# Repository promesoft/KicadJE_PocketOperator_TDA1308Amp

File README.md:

# KicadJE_PocketOperator_TDA1308Amp
TDA1308 based headphone power amp for Teenage Engineering PO series

# Version - REV A1
Tested Working - multi channel input
Not tested - sync

# Kicad 9

# Purpose AMP
- Amp and sync dist for PO TE boards
- Overcome the drop in audio level that happens when daisychaining the devices
- 
# Operation
## Amp 1
- 2 stereo in
- 1 mono / sync in
- 2 sync out
- 1 stereo headphone out
- power button

# Pictures

Components:
https://www.aliexpress.com/item/1005007083484555.html

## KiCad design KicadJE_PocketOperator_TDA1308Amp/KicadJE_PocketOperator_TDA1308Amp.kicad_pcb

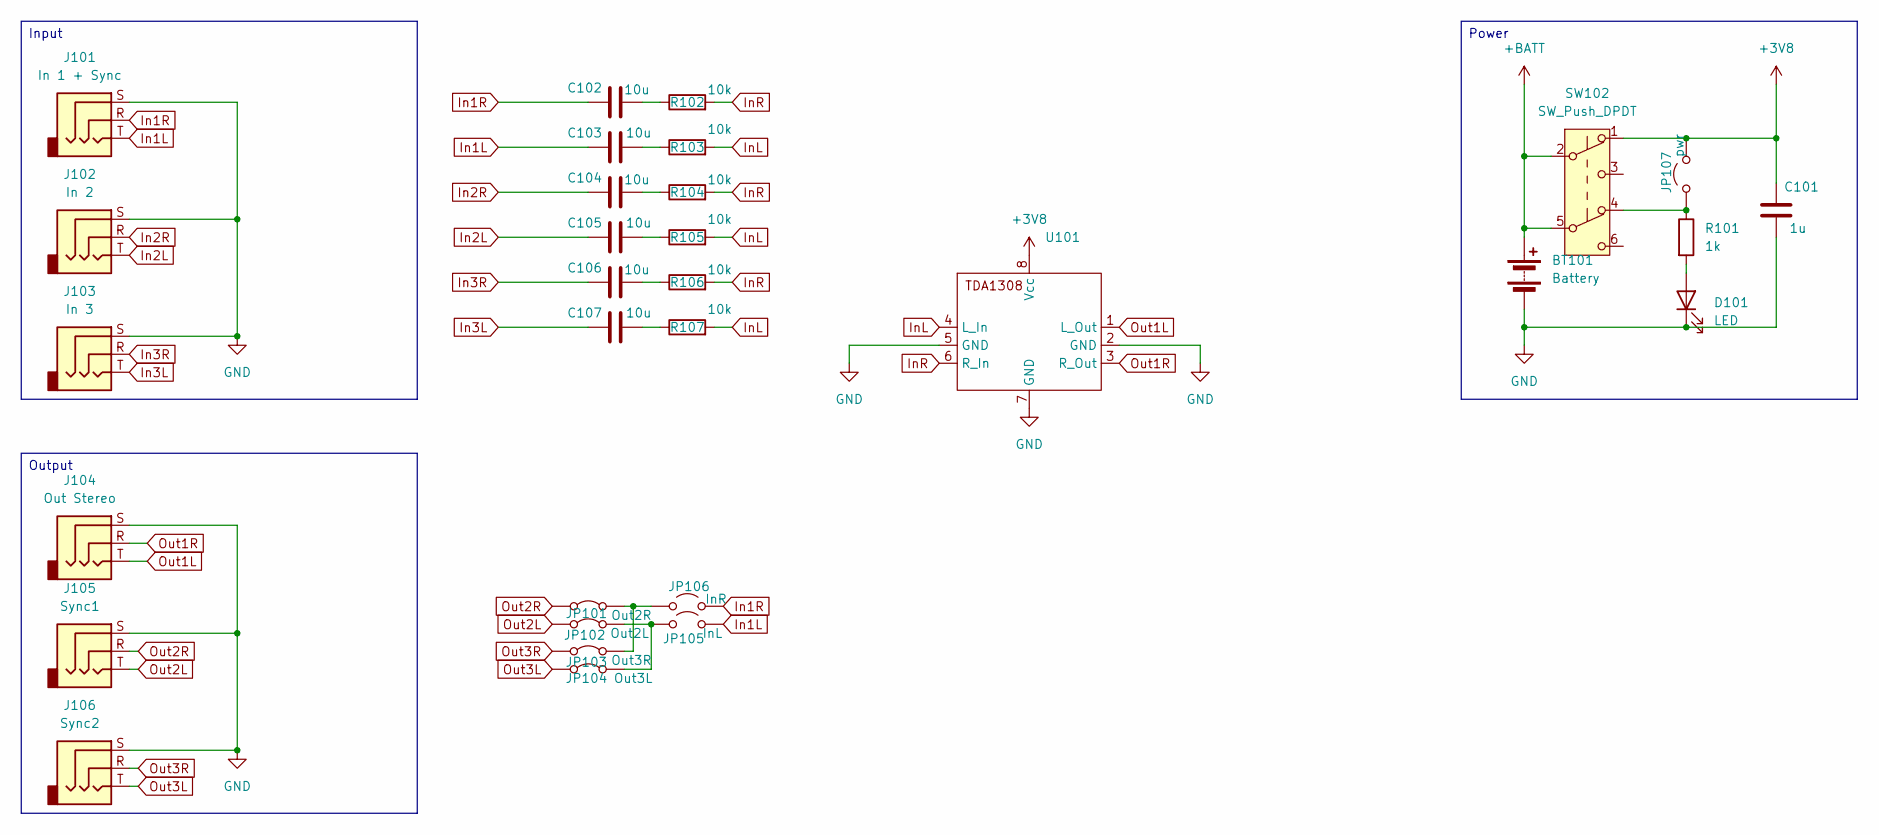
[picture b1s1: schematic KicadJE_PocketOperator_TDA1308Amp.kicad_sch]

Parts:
BT101: Battery; BatteryHolder_1xAA
C101: 1u; C_0805_2012Metric_Pad1.18x1.45mm_HandSolder
C102, C103, C104, C105, C106, C107: 10u; R_0805_2012Metric_Pad1.20x1.40mm_HandSolder
D101: LED; LED_0805_2012Metric_Pad1.15x1.40mm_HandSolder
J101: In 1 + Sync; Jack_3.5mm_Lumberg_1503_07_Horizontal
J102: In 2; Jack_3.5mm_Lumberg_1503_07_Horizontal
J103: In 3; Jack_3.5mm_Lumberg_1503_07_Horizontal
J104: Out Stereo; Jack_3.5mm_Lumberg_1503_07_Horizontal
J105: Sync1; Jack_3.5mm_Lumberg_1503_07_Horizontal
J106: Sync2; Jack_3.5mm_Lumberg_1503_07_Horizontal
JP101: Out2R; SolderJumper-2_P1.3mm_Bridged_RoundedPad1.0x1.5mm
JP102: Out2L; SolderJumper-2_P1.3mm_Bridged_RoundedPad1.0x1.5mm
JP103: Out3R; SolderJumper-2_P1.3mm_Bridged_RoundedPad1.0x1.5mm
JP104: Out3L; SolderJumper-2_P1.3mm_Bridged_RoundedPad1.0x1.5mm
JP105: InL; SolderJumper-2_P1.3mm_Open_RoundedPad1.0x1.5mm
JP106: InR; SolderJumper-2_P1.3mm_Open_RoundedPad1.0x1.5mm
JP107: pwr; SolderJumper-2_P1.3mm_Open_RoundedPad1.0x1.5mm
R101: 1k; R_0805_2012Metric_Pad1.20x1.40mm_HandSolder
R102, R103, R104, R105, R106, R107: 10k; R_0805_2012Metric_Pad1.20x1.40mm_HandSolder
SW102: SW_Push_DPDT; SW_Push_2P2T_Toggle_CK_PVA2OAH5xxxxxxV2
U101: TDA1308_PCB

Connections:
+3V8: C101.1, JP107.2 (B), SW102.1 (A), U101.8 (Vcc)
+BATT: BT101.1 (+), SW102.2 (B), SW102.5 (B)
GND: BT101.2 (-), C101.2, D101.1 (K), J101.S, J102.S, J103.S, J104.S, J105.S, J106.S, U101.2 (GND), U101.5 (GND), U101.7 (GND)
In1L: C103.1, J101.T, JP105.2 (B)
In1R: C102.1, J101.R, JP106.2 (B)
In2L: C105.1, J102.T
In2R: C104.1, J102.R
In3L: C107.1, J103.T
In3R: C106.1, J103.R
InL: R103.2, R105.2, R107.2, U101.4 (L_In)
InR: R102.2, R104.2, R106.2, U101.6 (R_In)
unnamed: C102.2, R102.1
unnamed: C103.2, R103.1
unnamed: C104.2, R104.1
unnamed: C105.2, R105.1
unnamed: C106.2, R106.1
unnamed: C107.2, R107.1
unnamed: D101.2 (A), R101.2
unnamed: JP101.2 (B), JP103.2 (B), JP106.1 (A)
unnamed: JP102.2 (B), JP104.2 (B), JP105.1 (A)
unnamed: JP107.1 (A), R101.1, SW102.4 (A)
Out1L: J104.T, U101.1 (L_Out)
Out1R: J104.R, U101.3 (R_Out)
Out2L: J105.T, JP102.1 (A)
Out2R: J105.R, JP101.1 (A)
Out3L: J106.T, JP104.1 (A)
Out3R: J106.R, JP103.1 (A)

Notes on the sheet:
Output
Power
Input

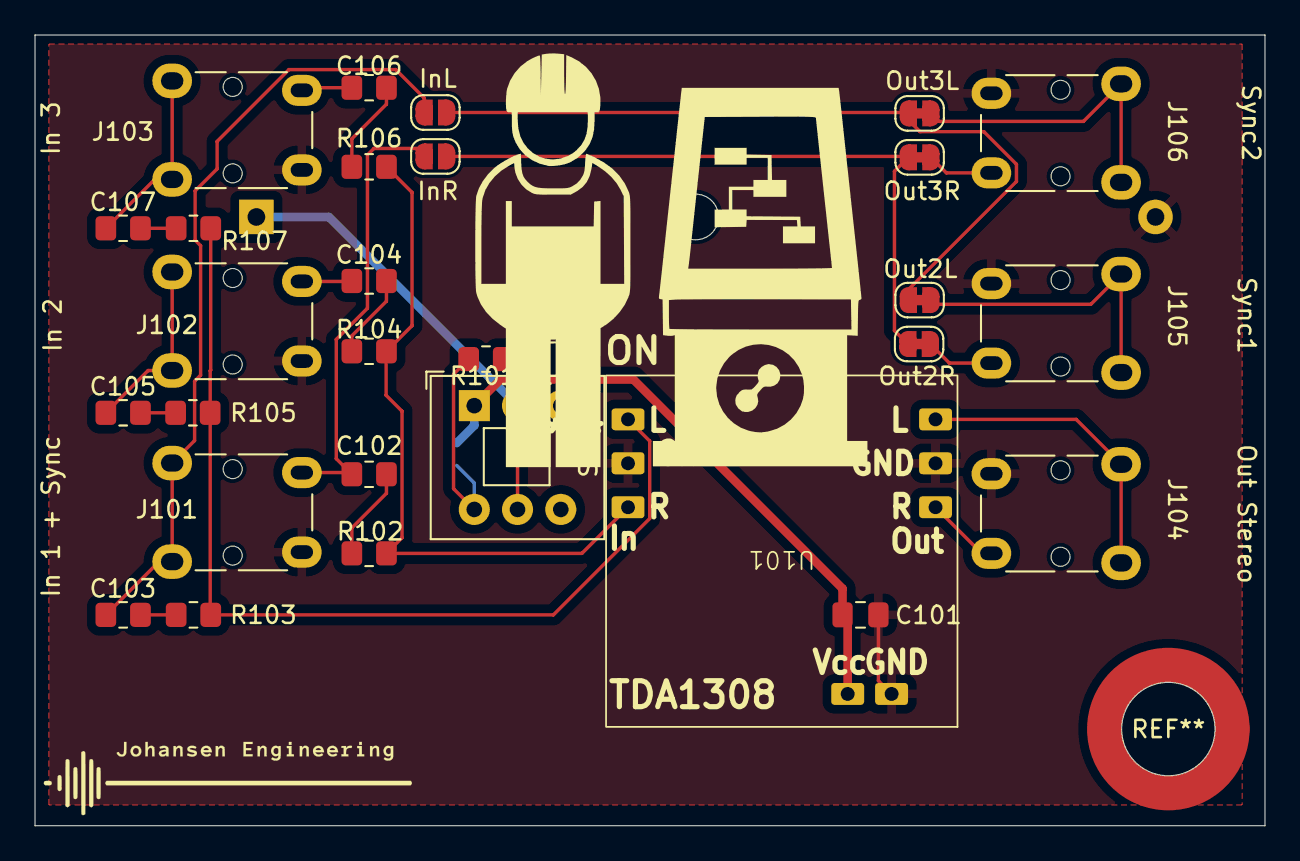
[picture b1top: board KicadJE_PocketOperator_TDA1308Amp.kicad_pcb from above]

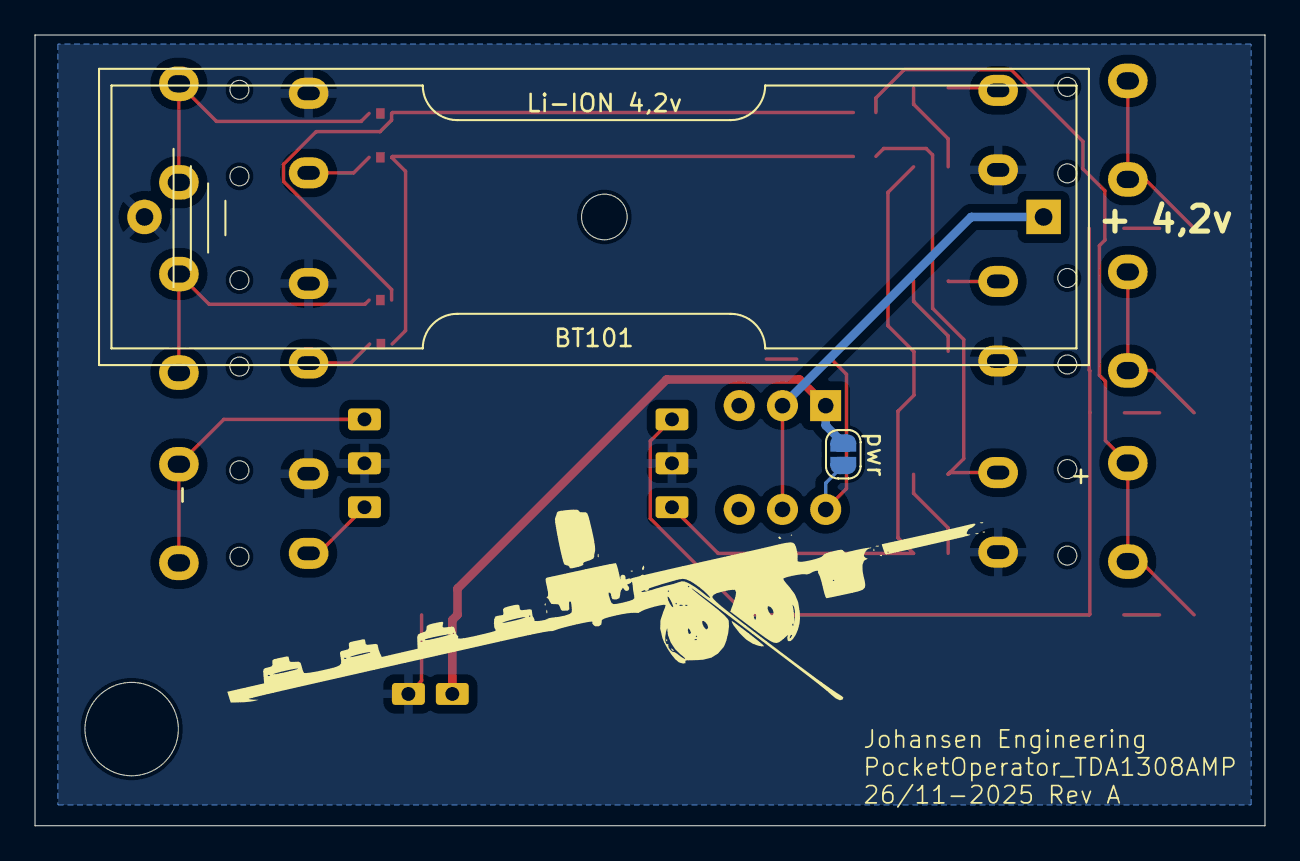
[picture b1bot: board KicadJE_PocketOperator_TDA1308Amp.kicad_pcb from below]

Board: 2 copper layers, 71.1 x 45.7 mm, 31 parts (2 on the bottom side), 27 nets.

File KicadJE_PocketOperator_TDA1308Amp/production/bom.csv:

Designator,Footprint,Quantity,Value,LCSC Part #
BT101,BatteryHolder_1xAA,1,Battery,
C101,0805,1,1u,
"C102, C103, C104, C105, C106, C107",0805,6,10u,
D101,0805,1,LED,
J101,Jack_3.5mm_Lumberg_1503_07_Horizontal,1,In 1 + Sync,
J102,Jack_3.5mm_Lumberg_1503_07_Horizontal,1,In 2,
J103,Jack_3.5mm_Lumberg_1503_07_Horizontal,1,In 3,
J104,Jack_3.5mm_Lumberg_1503_07_Horizontal,1,Out Stereo,
J105,Jack_3.5mm_Lumberg_1503_07_Horizontal,1,Sync1,
J106,Jack_3.5mm_Lumberg_1503_07_Horizontal,1,Sync2,
JP101,SolderJumper-2_P1.3mm_Bridged_RoundedPad1.0x1.5mm,1,Out2R,
JP102,SolderJumper-2_P1.3mm_Bridged_RoundedPad1.0x1.5mm,1,Out2L,
JP103,SolderJumper-2_P1.3mm_Bridged_RoundedPad1.0x1.5mm,1,Out3R,
JP104,SolderJumper-2_P1.3mm_Bridged_RoundedPad1.0x1.5mm,1,Out3L,
JP105,SolderJumper-2_P1.3mm_Open_RoundedPad1.0x1.5mm,1,InL,
JP106,SolderJumper-2_P1.3mm_Open_RoundedPad1.0x1.5mm,1,InR,
JP107,SolderJumper-2_P1.3mm_Open_RoundedPad1.0x1.5mm,1,pwr,
R101,0805,1,1k,
"R102, R103, R104, R105, R106, R107",0805,6,10k,
SW102,SW_Push_2P2T_Toggle_CK_PVA2OAH5xxxxxxV2,1,SW_Push_DPDT,
U101,TDA1308_PCB,1,~,

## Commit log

2025-11-26 Update README with project details and operation
    Expanded project description and added details about version, purpose, operation, and pictures.
2025-11-26 Add components link to README
    Added a link to components in the README.
2025-11-26 Project and sch started
2025-11-26 battery power
2025-11-26 TDA1308 footprint
2025-11-26 TDA1308 symbol
2025-11-26 Footprints Updated
2025-11-26 footprints placed
2025-11-26 Logo etc
    TDA symbol PSU GND swapped
    New logos
2025-11-26 Update KicadJE_PocketOperator_TDA1308Amp.kicad_pcb
    update TDA 1308 PWR correction
2025-11-26 Routed
2025-11-26 fabrication output
2025-11-26 sent to jlc
2025-12-17 pocketoperator2
2025-12-17 Add image pocketoperator2.jpg to README
2026-04-28 Update README with testing status
    Added testing status for multi-channel input and sync.
